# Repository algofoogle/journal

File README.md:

# Anton's Journal

This is a place where I will collect general notes and thoughts on projects I pick up ad-hoc,
or other stuff that takes my interest and I experiment with.

Create a new article with `make` or `make new` (same). Ensure this README is updated correctly at the end, too.

# Index

## 2019

<details>
<summary>Click to open:</summary>

*   [0001-2019-11-28.md](./0001-2019-11-28.md): Digispark tiny Arduino-based minimal USB device.
*   [0002-2019-12-02.md](./0002-2019-12-02.md): Digispark code experiments, Arduino basics, system requirements.
*   [0003-2019-12-03.md](./0003-2019-12-03.md): Digispark virtual keyboard experiments.
*   [0004-2019-12-04.md](./0004-2019-12-04.md): Stuff about installing Arduino libs.
*   ...TBC...
*   [0009-2019-12-19.md](./0009-2019-12-19.md): Quick update re DigiCDC (more minimal USB stuff).
</details>

## 2020

<details>
<summary>Click to open:</summary>

### A lot of 2020 was about FPGA/CPLD/Verilog stuff, starting with entry `0022`

*   [0010-2020-01-06.md](./0010-2020-01-06.md): Blender 3D SVG path offset extrusion, i.e. Straight Skeleton.
*   [0011-2020-01-07.md](./0011-2020-01-07.md): Geeetech A10 3D printer bed adhesion notes.
*   ...TBC...
*   [0021-2020-05-24.md](./0021-2020-05-24.md): FPGA/Verilog getting started; XC9572 CPLD board design initial notes.
*   [0022-2020-05-26.md](./0022-2020-05-26.md): CPLD board, KiCad notes, Xilinx ISE Webpack.
*   [0023-2020-05-29.md](./0023-2020-05-29.md): Lab setup, XC9572XL CPLD board prep notes.
*   [0024-2020-06-02.md](./0024-2020-06-02.md): Quick notes about JLCPCB and other PCB ideas.
*   [0025-2020-06-04.md](./0025-2020-06-04.md): NES Dev board ideas and some thoughts on STM32 types, speed, overclocking.
*   [0026-2020-06-06.md](./0026-2020-06-06.md): Initial tests of DP's XC9572XL CPLD board, Bus Pirate, XSVF player, JTAG.
*   [0027-2020-06-08.md](./0027-2020-06-08.md): Quick notes on my CPLD board, Xilinx ISE on Linux.
*   [0028-2020-06-09.md](./0028-2020-06-09.md): More Xilinx ISE and PACE stuff. Success!
*   [0029-2020-06-15.md](./0029-2020-06-15.md): Following fpga4fun.com on my CPLD board.
*   [0030-2020-06-17.md](./0030-2020-06-17.md): test05f/g/h (music) designs, and working around ISE/Fitter/Synth bugs.
*   [0031-2020-06-19.md](./0031-2020-06-19.md): test05h: Calculating notes.
*   [0032-2020-06-20.md](./0032-2020-06-20.md): CPLD optimisation/fitting and more music box stuff.
*   [0033-2020-06-21.md](./0033-2020-06-21.md): Quick note about starting a Pong-like design.
*   [0034-2020-06-22.md](./0034-2020-06-22.md): Basic VGA output working from by XC9572XL CPLD board.
*   ...TBC...
*   [0046-2020-07-22.md](./0046-2020-07-22.md): Starting CPLD t09a
*   [0047-2020-07-25.md](./0047-2020-07-25.md): CPLD t09a: VGA image from ROM plug-in board
*   [0048-2020-07-29.md](./0048-2020-07-29.md): CPLD t09c rough notes
*   [0049-2020-08-02.md](./0049-2020-08-02.md): CPLD t09d: ROM-based tile map VGA renderer.
*   [0050-2020-08-03.md](./0050-2020-08-03.md): Verilator and vgasim.
*   [0051-2020-08-04.md](./0051-2020-08-04.md): More Verilator: Register initialisation/randomisation.
*   ...TBC...
*   [0057-2020-08-10.md](./0057-2020-08-10.md): Quick notes about GT's (ZipCPU's) Verilator simulation models, re QSPIFLASHSIM.
*   [0058-2020-08-11.md](./0058-2020-08-11.md): Last from 2020: Some FPGA/CPLD/Verilog/Verilator final notes and thoughts about 6502 DMA/Video bus sharing.
</details>

## 2022

<details>
<summary>Click to open:</summary>

*   [0059-2022-04-02.md](./0059-2022-04-02.md): Restart from 2022: Some VirtualBox symlinks stuff under Windows 10 host.
*   [0060-2022-11-23.md](./0060-2022-11-23.md): Loose notes and next steps after Connectorama (ACUcard) first attempt.
</details>

## 2023

<details>
<summary>Click to open:</summary>

*   [0061-2023-04-16.md](./0061-2023-04-16.md): ASIC stuff with a focus on ray casting.
*   [0062-2023-04-17.md](./0062-2023-04-17.md): Fiddling with Raybox ideas.
*   [0063-2023-04-18.md](./0063-2023-04-18.md): Mostly notes about Verilog division and reciprocals.
*   [0064-2023-04-21.md](./0064-2023-04-21.md): Summary of basic fake rendering stuff, and a basic plan for what comes next.
*   [0065-2023-04-23.md](./0065-2023-04-23.md): Quick notes mostly about Verilog
*   [0066-2023-04-26.md](./0066-2023-04-26.md): Lots of notes about TT03 and running Tiny Tapeout GDS build locally
*   [0067-2023-04-27.md](./0067-2023-04-27.md): Some more quick notes about TT03
*   [0068-2023-04-28.md](./0068-2023-04-28.md): Starting fixed-point mode in raybox-app. Notes on VSCode C++ debugging.
*   [0069-2023-04-29.md](./0069-2023-04-29.md): Running Raybox on an FPGA.
*   [0070-2023-04-30.md](./0070-2023-04-30.md): Raybox starting Q16.16. Other future ideas.
*   [0071-2023-05-01.md](./0071-2023-05-01.md): Raybox wall edge glitch fixed! Q16.16 working. What next?
*   [0072-2023-05-02.md](./0072-2023-05-02.md): Raybox map grid boundary glitch fixed.
*   [0073-2023-05-03.md](./0073-2023-05-03.md): Raybox LZC alternatives. Rotation issues.
*   [0074-2023-05-04.md](./0074-2023-05-04.md): Diagnosing/fixing Raybox on FPGA.
*   [0075-2023-05-06.md](./0075-2023-05-06.md): Notes for some Raybox stuff to look at next
*   [0076-2023-05-07.md](./0076-2023-05-07.md): Raybox axis glitch fixed? Other ideas for host control
*   [0077-2023-05-09.md](./0077-2023-05-09.md): Raybox sim builds under Windows now and supports mouse rotation.
*   [0078-2023-05-10.md](./0078-2023-05-10.md): Raybox wall textures, thoughts on RAM
*   [0079-2023-05-12.md](./0079-2023-05-12.md): Raybox improved column rendering/scaling
*   [0080-2023-05-16.md](./0080-2023-05-16.md): Raybox starting work on sprites
*   [0081-2023-05-20.md](./0081-2023-05-20.md): First Raybox sprite seems to project OK
*   [0082-2023-05-22.md](./0082-2023-05-22.md): Raybox sprite extra scaling and screen 640-width
*   [0083-2023-05-23.md](./0083-2023-05-23.md): Tidying Raybox for targeting OpenLane
*   [0084-2023-05-24.md](./0084-2023-05-24.md): Merged Raybox sprites branch. Notes on OpenLane.
*   [0085-2023-05-25.md](./0085-2023-05-25.md): Raybox 64x64 map with multiple wall types supported
*   [0086-2023-05-26.md](./0086-2023-05-26.md): Quick notes on ideas for sending data to the FPGA
*   [0087-2023-05-27.md](./0087-2023-05-27.md): OpenLane experiments with reciprocal approximation design
*   [0088-2023-05-28.md](./0088-2023-05-28.md): Quick notes about LZC and cocotb
*   [0089-2023-06-05.md](./0089-2023-06-05.md): Notes about solo_squash tt03p5 submission
*   [0090-2023-06-06.md](./0090-2023-06-06.md): PC to DE0-Nano bridging ideas inc. IO expanders
*   [0091-2023-06-07.md](./0091-2023-06-07.md): Notes about STM32 USB and virtual COM
*   [0092-2023-06-08.md](./0092-2023-06-08.md): STM32 vs Raspberry Pi Pico
*   [0093-2023-06-09.md](./0093-2023-06-09.md): Follow along with Pi Pico C SDK guide
*   [0094-2023-06-12.md](./0094-2023-06-12.md): Pi Pico to DE0-Nano pin mapping
*   [0095-2023-06-14.md](./0095-2023-06-14.md): Pi Pico stdio coding on Wokwi
*   [0096-2023-06-17.md](./0096-2023-06-17.md): Getting Pico-DE0 REPL working just for GPIO reads
*   [0097-2023-06-18.md](./0097-2023-06-18.md): Pico-DE0 firmware supports basic I/O control now
*   [0098-2023-06-19.md](./0098-2023-06-19.md): Pico-DE0 improvements and readying for Raybox IO
*   [0099-2023-06-20.md](./0099-2023-06-20.md): Notes on Pico-DE0 speed
*   [0100-2023-06-21.md](./0100-2023-06-21.md): Basic plans for next steps in Pico-DE0 and Raybox
*   [0101-2023-06-22.md](./0101-2023-06-22.md): Working on raybox-bridge
*   [0102-2023-06-25.md](./0102-2023-06-25.md): Raybox-bridge time scheduling and USB transfer
*   [0103-2023-06-26.md](./0103-2023-06-26.md): Quick raybox-bridge notes and next steps
*   [0104-2023-06-27.md](./0104-2023-06-27.md): FPGA vga_cursor design works with raybox-bridge. Quartus project notes.
*   [0105-2023-06-29.md](./0105-2023-06-29.md): vga_cursor initial test findings
*   [0106-2023-06-30.md](./0106-2023-06-30.md): Quick update on vga_cursor with circle-cursor test
*   [0107-2023-07-02.md](./0107-2023-07-02.md): Notes on changing vga_cursor to SPI
*   [0108-2023-07-03.md](./0108-2023-07-03.md): vga_cursor now works via SPI
*   [0109-2023-07-06.md](./0109-2023-07-06.md): PicoDeo SPI /cursor command with raybox-bridge support
*   [0110-2023-07-07.md](./0110-2023-07-07.md): Raybox: DE0-Nano builds again. PicoDeo /rbvectors. Windows Verilator notes.
*   [0111-2023-07-10.md](./0111-2023-07-10.md): raybox-bridge basic FPS game state tracking
*   [0112-2023-07-11.md](./0112-2023-07-11.md): raybox-bridge sends vector (view) data, enabling KB/Mouse control in Raybox
*   [0113-2023-07-12.md](./0113-2023-07-12.md): Starting BOOP! game for Lily
*   [0114-2023-07-13.md](./0114-2023-07-13.md): Notes on next steps for Raybox
*   [0115-2023-07-14.md](./0115-2023-07-14.md): Quick notes on VGA DAC and 2D grid collision detection
*   [0116-2023-07-16.md](./0116-2023-07-16.md): raybox-game with basic collision detection
*   [0117-2023-07-18.md](./0117-2023-07-18.md): Thoughts on targeting Tiny Tapeout with Raybox
*   [0118-2023-07-19.md](./0118-2023-07-19.md): Some TT04 ideas
*   [0119-2023-07-22.md](./0119-2023-07-22.md): Let's get started with TT04
*   [0120-2023-07-24.md](./0120-2023-07-24.md): tt04-solo-squash next steps
*   [0121-2023-07-26.md](./0121-2023-07-26.md): Setting up tt04-solo-squash to use solo_squash submodule
*   [0122-2023-07-27.md](./0122-2023-07-27.md): tt04-solo-squash stuff
*   [0123-2023-08-14.md](./0123-2023-08-14.md): Quick update re raybox-zero
*   [0124-2023-08-16.md](./0124-2023-08-16.md): Another quick raybox-zero update
*   [0125-2023-08-18.md](./0125-2023-08-18.md): raybox-zero tracing works
*   [0126-2023-08-19.md](./0126-2023-08-19.md): tt04-raybox-zero started, but gds hardening crashes
*   [0127-2023-08-20.md](./0127-2023-08-20.md): Exploring tt04-raybox-zero synthesis, chasing yosys-abc bug
*   [0128-2023-08-21.md](./0128-2023-08-21.md): Starting tt04-reciprocal test
*   [0129-2023-08-22.md](./0129-2023-08-22.md): tt04-reciprocal findings and next steps on yosys-abc bug hunt
*   [0130-2023-08-23.md](./0130-2023-08-23.md): More yosys-abc bug hunting
*   [0131-2023-08-24.md](./0131-2023-08-24.md): raybox-zero: Improving the FSM
*   [0132-2023-08-25.md](./0132-2023-08-25.md): tt04-raybox-zero harden_test.sh script for stats
*   [0133-2023-08-26.md](./0133-2023-08-26.md): Setting up MPW8 VM again on a new laptop
*   [0134-2023-08-27.md](./0134-2023-08-27.md): raybox-zero SPI access to pov
*   [0135-2023-08-28.md](./0135-2023-08-28.md): raybox-zero sim kb/mouse control and partial POV SPI synth success
*   [0136-2023-08-29.md](./0136-2023-08-29.md): Working on wall_tracer changes
*   [0137-2023-08-30.md](./0137-2023-08-30.md): raybox-zero: Merging height_scaler
*   [0138-2023-08-31.md](./0138-2023-08-31.md): raybox-zero: Minor update
*   [0139-2023-09-01.md](./0139-2023-09-01.md): Improved harden_test, more test results
*   [0140-2023-09-02.md](./0140-2023-09-02.md): raybox-zero test005: Shared multiplier is a winner?
*   [0141-2023-09-03.md](./0141-2023-09-03.md): test006: shmul registered inputs; test007 reg rcp_in
*   [0142-2023-09-04.md](./0142-2023-09-04.md): test008: put a shmul in rcp and mainline test005
*   [0143-2023-09-05.md](./0143-2023-09-05.md): test009 (reducing pov bit ranges); test010 (fixed-point use Q10.10)
*   [0144-2023-09-06.md](./0144-2023-09-06.md): Work on implementing textures
*   [0145-2023-09-08.md](./0145-2023-09-08.md): Notes during TT04 final submission
*   [0146-2023-09-26.md](./0146-2023-09-26.md): VGA DAC PCB
*   [0147-2023-09-27.md](./0147-2023-09-27.md): What next: TT05 etc.
*   [0148-2023-09-28.md](./0148-2023-09-28.md): General updates, looking into VM speed
*   [0149-2023-09-30.md](./0149-2023-09-30.md): SPI flash ROM stuff
*   [0150-2023-10-02.md](./0150-2023-10-02.md): Reading SPI flash ROM using Bus Pirate
*   [0151-2023-10-03.md](./0151-2023-10-03.md): More SPI flash ROM stuff
*   [0152-2023-10-04.md](./0152-2023-10-04.md): Preparing for SPI flash ROM cocotb tests
*   [0153-2023-10-06.md](./0153-2023-10-06.md): SPI flash ROM FPGA tests
*   [0154-2023-10-07.md](./0154-2023-10-07.md): More SPI stuff
*   [0155-2023-10-09.md](./0155-2023-10-09.md): tt05-vga-spi-rom TT05 submission
*   [0156-2023-10-10.md](./0156-2023-10-10.md): tt05-vga-spi-rom improvements
*   [0157-2023-10-11.md](./0157-2023-10-11.md): tt05-vga-spi-rom and cocotb stuff
*   [0158-2023-10-13.md](./0158-2023-10-13.md): A bunch of tt05vsr (tt05-vga-spi-rom) tests
*   [0159-2023-10-14.md](./0159-2023-10-14.md): Continuing tt05vsr (tt05-vga-spi-rom) tests
*   [0160-2023-10-16.md](./0160-2023-10-16.md): Work on raybox-zero update for chipIgnite
*   [0161-2023-10-17.md](./0161-2023-10-17.md): Lots of chipIgnite notes
*   [0162-2023-10-20.md](./0162-2023-10-20.md): raybox-zero textures from external ROM
*   [0163-2023-10-22.md](./0163-2023-10-22.md): Working on QSPI
*   [0164-2023-10-23.md](./0164-2023-10-23.md): Implementing QSPI in tt05vsr and raybox-zero
*   [0165-2023-10-24.md](./0165-2023-10-24.md): raybox-zero OpenLane hardening
*   [0166-2023-10-26.md](./0166-2023-10-26.md): Preparing for chipIgnite
*   [0167-2023-10-27.md](./0167-2023-10-27.md): More prep for chipIgnite
*   [0168-2023-10-28.md](./0168-2023-10-28.md): Again more prep for chipIgnite
*   [0169-2023-10-30.md](./0169-2023-10-30.md): Snippets for other modes of top_ew_algofoogle
*   [0170-2023-10-31.md](./0170-2023-10-31.md): top_ew_algofoogle next steps
*   [0171-2023-11-03.md](./0171-2023-11-03.md): Getting down to the final steps for chipIgnite
*   [0172-2023-11-04.md](./0172-2023-11-04.md): Some fixes to raybox-zero-caravel
*   [0173-2023-11-18.md](./0173-2023-11-18.md): Analog start: installing xschem
*   [0174-2023-11-19.md](./0174-2023-11-19.md): sky130 analog simulation with xschem
*   [0175-2023-11-20.md](./0175-2023-11-20.md): More xschem and sky130
*   [0176-2023-11-22.md](./0176-2023-11-22.md): Tiny update re xschem/sky130
*   [0177-2023-11-27.md](./0177-2023-11-27.md): GFMPW-1 test (gf180mcu)
*   [0178-2023-11-28.md](./0178-2023-11-28.md): GFMPW-1 attempt at raybox-zero
*   [0179-2023-11-30.md](./0179-2023-11-30.md): Quick update re GFMPW-1 attempts
*   [0180-2023-12-01.md](./0180-2023-12-01.md): GFMPW-1 raybox-zero hardening
*   [0181-2023-12-02.md](./0181-2023-12-02.md): Getting algofoogle-multi-caravel up to efabless
*   [0182-2023-12-03.md](./0182-2023-12-03.md): GFMPW-1: Trying to fix UPW harden for gf180-rbz-fsm
*   [0183-2023-12-04.md](./0183-2023-12-04.md): Continue trying to fix rbz-fsm harden for GF180
*   [0184-2023-12-05.md](./0184-2023-12-05.md): First rough success hardening raybox-zero-fsm/UPW
*   [0185-2023-12-06.md](./0185-2023-12-06.md): Mux for GFMPW-1 group submission
*   [0186-2023-12-08.md](./0186-2023-12-08.md): Improving GFMPW-1 muti-project mux and layout
*   [0187-2023-12-09.md](./0187-2023-12-09.md): GFMPW-1 mux and group plan
*   [0188-2023-12-10.md](./0188-2023-12-10.md): GFMPW-1 Finalisation plan for today
*   [0189-2023-12-11.md](./0189-2023-12-11.md): GFMPW-1 finalisation
</details>

## 2024

*   [0190-2024-01-17.md](./0190-2024-01-17.md): PCB assembly with JLC PCB
*   [0191-2024-01-31.md](./0191-2024-01-31.md): Soldering QFNs and GFMPW0 bring-up
*   [0192-2024-02-02.md](./0192-2024-02-02.md): More GFMPW0 bringup prep and other notes
*   [0193-2024-02-03.md](./0193-2024-02-03.md): GFMPW0 smoke test
*   [0194-2024-02-05.md](./0194-2024-02-05.md): Getting TT03p5 ready for demo
*   [0195-2024-03-23.md](./0195-2024-03-23.md): Coming back to life (mostly about a new MPW9 VM)
*   [0196-2024-03-30.md](./0196-2024-03-30.md): TT04 raybox-zero test prep
*   [0197-2024-04-02.md](./0197-2024-04-02.md): Diagnosing tt04-raybox-zero ASIC malfunction
*   [0198-2024-04-03.md](./0198-2024-04-03.md): TT04 bug GL sim; fix VBox VT-x; analog stuff
*   [0199-2024-04-04.md](./0199-2024-04-04.md): Quick update: sky130 and Tiny Tapeout analog design
*   [0200-2024-04-05.md](./0200-2024-05-01.md): Belated update (TT chips, and analog)
*   [0201-2024-05-11.md](./0201-2024-05-11.md): Warming up for TT07 (tt-vga-fun)
*   [0202-2024-05-15.md](./0202-2024-05-15.md): Full layout simulation of tt06-grab-bag
*   [0203-2024-05-20.md](./0203-2024-05-20.md): ngspice full-circuit simulation results and improvements
*   [0204-2024-05-25.md](./0204-2024-05-25.md): Prep resubmission of TT04's raybox-zero to TT07
*   [0205-2024-05-30.md](./0205-2024-05-30.md): Very rough mixed notes about TT07 and starting TT04 testing
*   [0206-2024-06-26.md](./0206-2024-06-26.md): Trying out Efabless eval board and generic Caravel chip
*   [0207-2024-06-28.md](./0207-2024-06-28.md): Testing Caravel chips with HKDebug and the Efabless Eval board
*   [0208-2024-07-05.md](./0208-2024-07-05.md): Trying out CI2311 chips
*   [0209-2024-07-23.md](./0209-2024-07-23.md): Review original binary-weighted current-switching DAC
*   [0210-2024-08-09.md](./0210-2024-08-09.md): Current steering DAC experiments
*   [0211-2024-08-09.md](./0211-2024-08-09.md): Start tt08-vga-fun repo
*   [0212-2024-08-11.md](./0212-2024-08-11.md): Creating layout for tt08-vga-fun's CSDAC
*   [0213-2024-08-16.md](./0213-2024-08-16.md): Completed csdac_nom initial layout for tt08-vga-fun
*   [0214-2024-08-17.md](./0214-2024-08-17.md): Integrating digital and analog blocks in tt08-vga-fun
*   [0215-2024-08-21.md](./0215-2024-08-21.md): New 3x DAC layout and simulation for tt08-vga-fun
*   [0216-2024-08-23.md](./0216-2024-08-23.md): Notes for tt08-vga-fun finalisation inc. segmented CSDAC
*   [0217-2024-09-29.md](./0217-2024-09-29.md): Notes on CI2311 and GFMPW-1 versions of raybox-zero
*   [0218-2024-10-05.md](./0218-2024-10-05.md): GFMPW-1 basic bring-up
*   [0219-2024-10-07.md](./0219-2024-10-07.md): GFMPW-1 bring-up (continued)
*   [0220-2024-10-11.md](./0220-2024-10-11.md): Raybox-zero running on GFMPW-1
*   [0221-2024-10-11.md](./0221-2024-10-11.md): Quick first attempt at TTIHP0p2
*   [0222-2024-11-11.md](./0222-2024-11-11.md): Belated update for TTIHP0p2 and TT09 submissions
*   [0223-2024-11-12.md](./0223-2024-11-12.md): Ideas for future raybox-zero versions, inc. pinout changes
*   [0224-2024-12-05.md](./0224-2024-12-05.md): Rough notes for RBZ and TT06 Analog VGA testing prep

## 2025

*   [0225-2025-01-12.md](./0225-2025-01-12.md): Initial tt06-grab-bag Analog VGA bring-up
*   [0226-2025-02-20.md](./0226-2025-02-20.md): tt06-grab-bag Analog VGA works!
*   [0227-2025-02-25.md](./0227-2025-02-25.md): Efabless shutdown and old notes for TT10 local hardening
*   [0228-2025-03-27.md](./0228-2025-03-27.md): Testing some Tiny Tapeout 7 projects
*   [0229-2025-04-01.md](./0229-2025-04-01.md): tt07-raybox-zero testing (with textures)
*   [0230-2025-04-09.md](./0230-2025-04-09.md): More tt07-raybox-zero testing
*   [0231-2025-04-11.md](./0231-2025-04-11.md): TT06 auto demo; IHP "Antonalog" DAC & ring osc DAC + sim; TTCAD25a & RBZ update notes
*   [0232-2025-09-28.md](./0232-2025-09-28.md): Tiny Tapeouts from June to September
*   [0233-2025-09-28.md](./0233-2025-09-28.md): ttsky25a-vga-matrix-dac
*   [0234-2025-11-11.md](./0234-2025-11-11.md): ttsky25b-vga-matrix-dac (revisited)
*   [0235-2025-11-25.md](./0235-2025-11-25.md): ttgf0p2 submissions

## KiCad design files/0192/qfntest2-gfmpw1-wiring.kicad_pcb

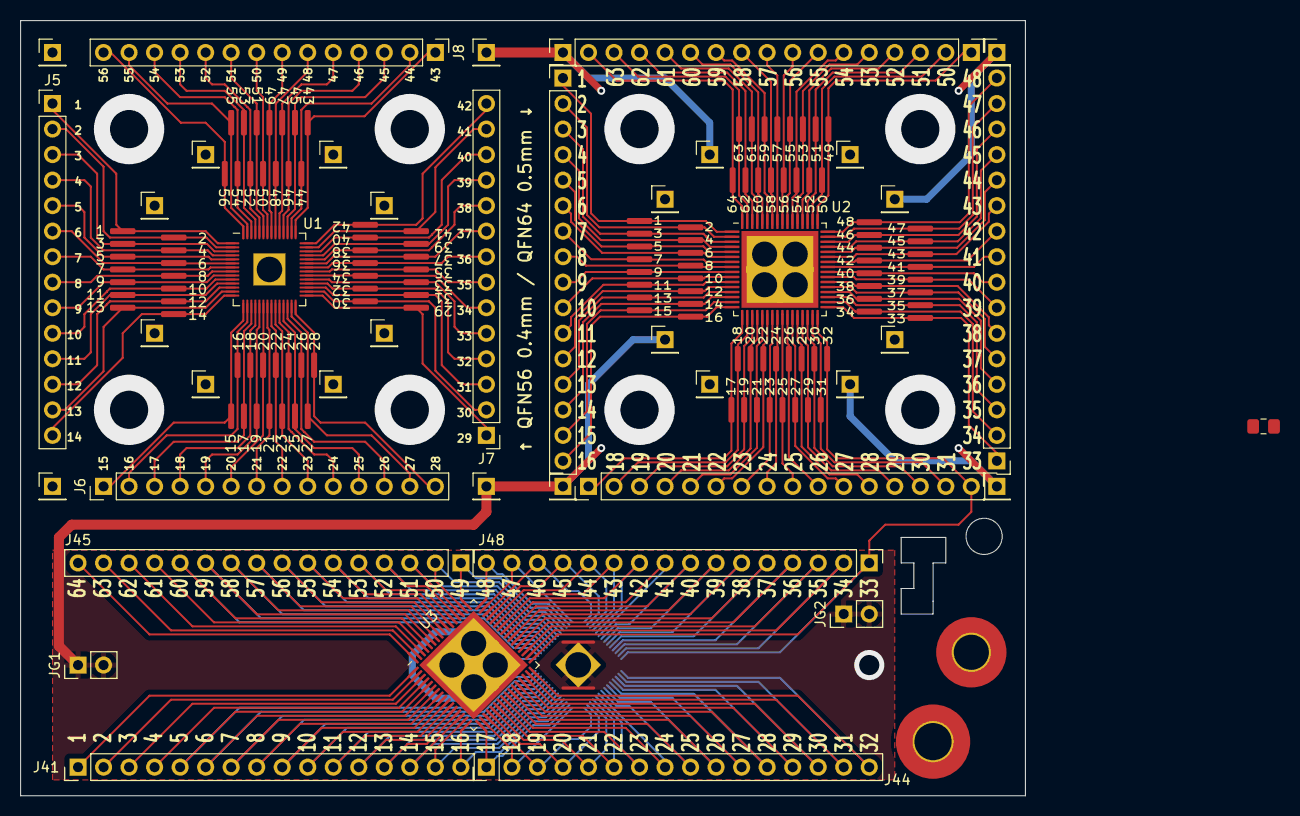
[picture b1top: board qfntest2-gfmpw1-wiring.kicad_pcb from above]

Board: 2 copper layers, 100.0 x 77.1 mm, 50 parts (1 on the bottom side), 184 nets.

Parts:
J1, J2, J3, J4: Conn_01x14; Anton_Pads_01x14_1.27mm_SMD
J5, J6, J7, J8: Conn_01x14; PinHeader_1x14_P2.54mm_Vertical
J9, J10, J11, J12, J13, J14, J15, J16, J17, J18, J19, J20, J29, J30, J31, J32, J33, J34, J35, J36, J37, J38, J39, J40: Conn_01x01; PinHeader_1x01_P2.54mm_Vertical
J21, J22, J23, J24: Conn_01x16; Anton_Pads_01x16_1.27mm_SMD
J25, J26, J27, J28, J41, J44, J45, J48: Conn_01x16; PinHeader_1x16_P2.54mm_Vertical
JG1, JG2: Conn_01x02; PinHeader_1x02_P2.54mm_Vertical
U1, U4: QFN-56-1EP_7x7mm_P0.4mm_EP3.2x3.2mm-HOLE
U2, U3: QFN-64-1EP_9x9mm_P0.5mm_EP7.65x7.65mm-HOLE

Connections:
/U4_01: J44.16, U3.32, U4.1
/U4_02: J44.15, U3.31, U4.2
/U4_03: J44.14, U3.30, U4.3
/U4_04: J44.13, U3.29, U4.4
/U4_05: J44.12, U3.28, U4.5
/U4_06: J44.11, U3.27, U4.6
/U4_07: J44.10, U3.26, U4.7
/U4_08: J44.9, U3.25, U4.8
/U4_09: J44.8, U3.24, U4.9
/U4_10: J44.7, U3.23, U4.10
/U4_11: J44.6, U3.22, U4.11
/U4_12: J44.5, U3.21, U4.12
/U4_13: J44.4, U3.20, U4.13
/U4_14: J44.3, U3.19, U4.14
/U4_15: J44.2, U3.18, U4.15
/U4_16: J44.1, U3.17, U4.16
/U4_17: J41.16, U3.16, U4.17
/U4_18: J41.15, U3.15, U4.18
/U4_19: J41.14, U3.14, U4.19
/U4_20: J41.13, U3.13, U4.20
/U4_21: J41.12, U3.12, U4.21
/U4_22: J41.11, U3.11, U4.22
/U4_23: J41.10, U3.10, U4.23
/U4_24: J41.9, U3.9, U4.24
/U4_25: J41.8, U3.8, U4.25
/U4_26: J41.7, U3.7, U4.26
/U4_27: J41.6, U3.6, U4.27
/U4_28: J41.5, U3.5, U4.28
/U4_29: J45.12, U3.60, U4.29
/U4_30: J45.11, U3.59, U4.30
/U4_31: J45.10, U3.58, U4.31
/U4_32: J45.9, U3.57, U4.32
/U4_33: J45.8, U3.56, U4.33
/U4_34: J45.7, U3.55, U4.34
/U4_35: J45.6, U3.54, U4.35
/U4_36: J45.5, U3.53, U4.36
/U4_37: J45.4, U3.52, U4.37
/U4_38: J45.3, U3.51, U4.38
/U4_39: J45.2, U3.50, U4.39
/U4_40: J45.1, U3.49, U4.40
/U4_41: J48.16, U3.48, U4.41
/U4_42: J48.15, U3.47, U4.42
/U4_43: J48.14, U3.46, U4.43
/U4_44: J48.13, U3.45, U4.44
/U4_45: J48.12, U3.44, U4.45
/U4_46: J48.11, U3.43, U4.46
/U4_47: J48.10, U3.42, U4.47
/U4_48: J48.9, U3.41, U4.48
/U4_49: J48.8, U3.40, U4.49
/U4_50: J48.7, U3.39, U4.50
/U4_51: J48.6, U3.38, U4.51
/U4_52: J48.5, U3.37, U4.52
/U4_53: J48.4, U3.36, U4.53
/U4_54: J48.3, U3.35, U4.54
/U4_55: J48.2, U3.34, U4.55
/U4_56: J22.16, J26.16, J48.1, U2.32, U3.33, U4.56
GND: J9.1, J10.1, J11.1, J12.1, J13.1, J14.1, J15.1, J16.1, J17.1, J18.1, J19.1, J20.1, J29.1, J30.1, J31.1, J32.1, J33.1, J34.1, J35.1, J36.1, J37.1, J38.1, J39.1, J40.1, JG1.1, JG1.2, JG2.1, JG2.2, U1.57 (GND), U2.65 (Foot), U3.65 (Foot), U4.57 (GND)
unnamed: J1.1, J5.1, U1.1
unnamed: J1.2, J5.2, U1.2
unnamed: J1.3, J5.3, U1.3
unnamed: J1.4, J5.4, U1.4
unnamed: J1.5, J5.5, U1.5
unnamed: J1.6, J5.6, U1.6
unnamed: J1.7, J5.7, U1.7
unnamed: J1.8, J5.8, U1.8
unnamed: J1.9, J5.9, U1.9
unnamed: J1.10, J5.10, U1.10
unnamed: J1.11, J5.11, U1.11
unnamed: J1.12, J5.12, U1.12
unnamed: J1.13, J5.13, U1.13
unnamed: J1.14, J5.14, U1.14
unnamed: J2.1, J6.1, U1.15
unnamed: J2.2, J6.2, U1.16
unnamed: J2.3, J6.3, U1.17
unnamed: J2.4, J6.4, U1.18
unnamed: J2.5, J6.5, U1.19
unnamed: J2.6, J6.6, U1.20
unnamed: J2.7, J6.7, U1.21
unnamed: J2.8, J6.8, U1.22
unnamed: J2.9, J6.9, U1.23
unnamed: J2.10, J6.10, U1.24
unnamed: J2.11, J6.11, U1.25
unnamed: J2.12, J6.12, U1.26
unnamed: J2.13, J6.13, U1.27
unnamed: J2.14, J6.14, U1.28
unnamed: J3.1, J7.1, U1.29
unnamed: J3.2, J7.2, U1.30
unnamed: J3.3, J7.3, U1.31
unnamed: J3.4, J7.4, U1.32
unnamed: J3.5, J7.5, U1.33
unnamed: J3.6, J7.6, U1.34
unnamed: J3.7, J7.7, U1.35
unnamed: J3.8, J7.8, U1.36
unnamed: J3.9, J7.9, U1.37
unnamed: J3.10, J7.10, U1.38
unnamed: J3.11, J7.11, U1.39
unnamed: J3.12, J7.12, U1.40
unnamed: J3.13, J7.13, U1.41
unnamed: J3.14, J7.14, U1.42
unnamed: J4.1, J8.1, U1.43
unnamed: J4.2, J8.2, U1.44
unnamed: J4.3, J8.3, U1.45
unnamed: J4.4, J8.4, U1.46
unnamed: J4.5, J8.5, U1.47
unnamed: J4.6, J8.6, U1.48
unnamed: J4.7, J8.7, U1.49
unnamed: J4.8, J8.8, U1.50
unnamed: J4.9, J8.9, U1.51
unnamed: J4.10, J8.10, U1.52
unnamed: J4.11, J8.11, U1.53
unnamed: J4.12, J8.12, U1.54
unnamed: J4.13, J8.13, U1.55
unnamed: J4.14, J8.14, U1.56
unnamed: J21.1, J25.1, U2.1
unnamed: J21.2, J25.2, U2.2
unnamed: J21.3, J25.3, U2.3
unnamed: J21.4, J25.4, U2.4
unnamed: J21.5, J25.5, U2.5
unnamed: J21.6, J25.6, U2.6
unnamed: J21.7, J25.7, U2.7
unnamed: J21.8, J25.8, U2.8
unnamed: J21.9, J25.9, U2.9
unnamed: J21.10, J25.10, U2.10
unnamed: J21.11, J25.11, U2.11
unnamed: J21.12, J25.12, U2.12
unnamed: J21.13, J25.13, U2.13
unnamed: J21.14, J25.14, U2.14
unnamed: J21.15, J25.15, U2.15
unnamed: J21.16, J25.16, U2.16
unnamed: J22.1, J26.1, U2.17
unnamed: J22.2, J26.2, U2.18
unnamed: J22.3, J26.3, U2.19
unnamed: J22.4, J26.4, U2.20
unnamed: J22.5, J26.5, U2.21
unnamed: J22.6, J26.6, U2.22
unnamed: J22.7, J26.7, U2.23
unnamed: J22.8, J26.8, U2.24
unnamed: J22.9, J26.9, U2.25
unnamed: J22.10, J26.10, U2.26
unnamed: J22.11, J26.11, U2.27
unnamed: J22.12, J26.12, U2.28
unnamed: J22.13, J26.13, U2.29
unnamed: J22.14, J26.14, U2.30
unnamed: J22.15, J26.15, U2.31
unnamed: J23.1, J27.1, U2.33
unnamed: J23.2, J27.2, U2.34
unnamed: J23.3, J27.3, U2.35
unnamed: J23.4, J27.4, U2.36
unnamed: J23.5, J27.5, U2.37
unnamed: J23.6, J27.6, U2.38
unnamed: J23.7, J27.7, U2.39
unnamed: J23.8, J27.8, U2.40
unnamed: J23.9, J27.9, U2.41
unnamed: J23.10, J27.10, U2.42
unnamed: J23.11, J27.11, U2.43
unnamed: J23.12, J27.12, U2.44
unnamed: J23.13, J27.13, U2.45
unnamed: J23.14, J27.14, U2.46
unnamed: J23.15, J27.15, U2.47
unnamed: J23.16, J27.16, U2.48
unnamed: J24.1, J28.1, U2.49
unnamed: J24.2, J28.2, U2.50
unnamed: J24.3, J28.3, U2.51
unnamed: J24.4, J28.4, U2.52
unnamed: J24.5, J28.5, U2.53
unnamed: J24.6, J28.6, U2.54
unnamed: J24.7, J28.7, U2.55
unnamed: J24.8, J28.8, U2.56
unnamed: J24.9, J28.9, U2.57
unnamed: J24.10, J28.10, U2.58
unnamed: J24.11, J28.11, U2.59
unnamed: J24.12, J28.12, U2.60
unnamed: J24.13, J28.13, U2.61
unnamed: J24.14, J28.14, U2.62
unnamed: J24.15, J28.15, U2.63
unnamed: J24.16, J28.16, U2.64
unnamed: J41.1, U3.1
unnamed: J41.2, U3.2
unnamed: J41.3, U3.3
unnamed: J41.4, U3.4
unnamed: J45.13, U3.61
unnamed: J45.14, U3.62
unnamed: J45.15, U3.63
unnamed: J45.16, U3.64

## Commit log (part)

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2023-05-02 0072: Raybox map grid boundary glitch fixed
2023-05-02 Minor update to 0072
2023-05-04 0074: Ideas to diagnose/fix Raybox on FPGA
2023-05-04 Updates to 0073 re LZC tests and other theories
2023-05-06 0075: Notes for some Raybox stuff to look at next
2023-05-07 0076: Raybox axis glitch fixed? Other ideas for host control
2023-05-11 0078: Raybox wall textures, thoughts on RAM
2023-05-11 Images for 0078
2023-05-11 Minor edit
2023-05-12 0079: Raybox improved column rendering/scaling
2023-05-20 Starting 0081
2023-05-21 0081: First Raybox sprite seems to project OK
2023-05-23 0083: Tidying Raybox for targeting OpenLane
2023-05-24 0084: Merged Raybox sprites branch. Notes on OpenLane
2023-05-26 0086: Quick notes on ideas for sending data to the FPGA
2023-05-28 0087: OpenLane experiments with reciprocal approximation design
2023-06-05 0089: Notes about solo_squash tt03p5 submission
2023-06-07 0091: Notes about STM32 USB and virtual COM
2023-06-08 0092: STM32 vs Raspberry Pi Pico
2023-06-09 0093: Follow along with Pi Pico C SDK guide
2023-06-09 Updating 0093 re Pi Pico basic USB
2023-06-12 0094 updates
2023-06-12 Adding hero image to 0094
2023-06-14 0095 updates
2023-06-15 Updating README a bit for older entries
2023-06-17 0096: Getting Pico-DE0 REPL working just for GPIO reads
2023-06-17 Just testing...
2023-06-17 0096 has link to previous journal in preamble now
2023-06-17 Update 0096, plus some backlinks, and improve Makefile
2023-06-17 Makefile minor correction
2023-06-17 0096 updated for extra pico_de0 firmware options
2023-06-19 0098: Pico-DE0 improvements and readying for Raybox IO
2023-06-19 Update 0098 re python client started
2023-06-20 0099: Notes on Pico-DE0 speed
2023-06-22 0101: Working on raybox-bridge
2023-06-22 0101 update
2023-06-25 0102: Raybox-bridge time scheduling and USB transfer
2023-06-26 0103: Quick raybox-bridge notes
2023-06-27 0104: FPGA vga_cursor design works with raybox-bridge. Quartus project notes
2023-06-29 0105: vga_cursor initial test findings
2023-06-30 0106: Quick update on vga_cursor with circle-cursor test
2023-06-30 Update 0106 with pictures
2023-07-02 0107 updates for USE_SPI update and next steps
2023-07-03 0108: vga_cursor now works via SPI
2023-07-07 0110: Raybox: DE0-Nano builds again. Windows Verilator notes
2023-07-07 Update 0110 with PicoDeo /rbvectors info
2023-07-10 0111: raybox-bridge basic FPS game state tracking
2023-07-11 Update 0112 re Raybox now actually receiving SPI vectors data
2023-07-12 0113: Starting BOOP! game for Lily
2023-07-14 0115: Quick notes on VGA DAC and 2D grid collision detection
2023-07-16 0116: raybox-game with basic collision detection
2023-07-19 0118: Some TT04 ideas
2023-07-22 0119: Let's get started with TT04
2023-07-24 0120 updates
2023-07-26 0121: Setting up tt04-solo-squash to use solo_squash submodule
2023-07-27 0122: tt04-solo-squash stuff
2023-07-27 Update 0122
2023-08-16 Minor extra info on 0123
2023-08-16 0124: Another quick raybox-zero update
2023-08-16 More updates to 0124
2023-08-18 0125: raybox-zero tracing works
2023-08-18 More notes on 0125
2023-08-19 Update 0126 for trying to locally run hardening per TT04
2023-08-19 Update 0126 with progress on local hardening
2023-08-20 Update 0127 with new OpenLane container launch instructions
2023-08-20 Minor update to 0127
2023-08-21 0128: Starting tt04-reciprocal test
2023-08-22 0129: tt04-reciprocal findings and next steps on yosys-abc bug hunt
2023-08-23 Lots of updates on 0129 and 2308B
2023-08-23 0130: More yosys-abc bug hunting
2023-08-24 0131: raybox-zero: Improving the FSM
2023-08-24 Logging initial results for 0131
2023-08-26 0133: Setting up MPW8 VM again on a new laptop
2023-08-26 Updates to 0133 re MPW8 VM setup
2023-08-27 Update 0133 re VSCode
2023-08-27 0134: raybox-zero SPI access to pov
2023-08-28 Update 0135 with synth results
2023-08-29 0136: Working on wall_tracer changes
2023-08-29 Updates to 0136 re working shared_reciprocal
2023-08-29 Update 0136: Adding stats before shared_reciprocal
2023-08-30 0137: raybox-zero: Merging height_scaler
2023-08-30 Update 0137 with stats from debug logic baked in
2023-08-31 0138: raybox-zero: Minor update
2023-09-01 Update 0139 with baseline harden_test results: height_scaler merged into wall_tracer
2023-09-01 Update 0139: Results for test001 (Merged TraceStep/TraceTest; commented out 'tex' logic)
2023-09-01 Update 0139: Add extra test001 data
2023-09-01 Update 0139: Results for test002: registered vdist
2023-09-01 Update 0139: Adding test004 results and a couple other ideas
2023-09-02 0140: raybox-zero test005: Shared multiplier is a winner?
2023-09-03 0141: test006
2023-09-03 Update 0141 with test006 alternate
2023-09-04 0142: test008: put a shmul in rcp
2023-09-04 Minor 0142 update
2023-09-04 Update 0142 after mainlining test005
2023-09-05 Update 0143 with extra test009 results
2023-09-05 Update 0143 to describe findings of test009-2, -3, and -4
2023-09-05 Update 0143 with GDS image of 2x2 and comments on power
2023-09-05 Minor update to 0143
2023-09-06 Update 0143: test010-4 Q10.10 results
2023-09-06 Start 0144: Work on implementing texturs
2023-09-26 Add tip 2309A
2023-09-26 0146: VGA DAC PCB
2023-09-27 0147: What next: TT05 etc.
2023-09-27 Update 0147 with notes about wall/sprite memory access
2023-09-30 Update 0148 with recent fixes and next steps
2023-09-30 0149: SPI flash ROM stuff
2023-10-02 Update 0149 with a few other links
2023-10-02 0150: Reading SPI flash ROM using Bus Pirate
2023-10-03 0151: More SPI flash ROM stuff
2023-10-03 Stub 0152
2023-10-04 Tip 2310A: Setting up Python on Windows with VSCode
2023-10-06 0153: SPI flash ROM FPGA tests
2023-10-06 Update 0153: Add ROM data sample
2023-10-07 0154: More SPI stuff
2023-10-07 Update 0154 a little
2023-10-07 Update 0154 re stored-vs-direct and other next steps
2023-10-08 Stub 0155: Continuing SPI test design
2023-10-09 Stub 0156: tt05-vga-spi-rom improvements
2023-10-09 Minor updates to 0155
2023-10-10 Tip 2310B (cocotb, iverilog, gtkwave on Windows); 0156 lots of cocotb testing doco
2023-10-10 Various minor updates
2023-10-10 Minor 0156 update re spiflash
2023-10-11 Adding to 0157
2023-10-12 Finish 0157
2023-10-14 0158: A bunch of tt05vsr (tt05-vga-spi-rom) tests
2023-10-14 Stub 0159
2023-10-14 Lots of updates for 0159 test results
2023-10-14 Updated 0159 a little bit
2023-10-16 0160: Work on raybox-zero update for chipIgnite
2023-10-16 Update 0160
2023-10-20 0161: Lots of chipIgnite notes
2023-10-20 Stub 0162
2023-10-20 Update 0162
2023-10-20 Update 0162: First SPI write test of wall texture test image (wolfwall)
2023-10-20 Update 0162: Fix texture orientation and light/dark tint
2023-10-20 Update 0162 with notes re QSPI
2023-10-22 Stub 0163
2023-10-22 0163: Working on QSPI - progress update
2023-10-22 Update 0163: Many more SQPI notes
2023-10-22 Update 0163: TL;DR added for QSPI process
2023-10-22 Minor 0163 update
2023-10-23 Update 0164 with plan for tt05vsr QSPI reads
2023-10-23 0164: Implementing QSPI in tt05vsr and raybox-zero
2023-10-24 Update 0165 re plan, Quartus PLL, SPI glitch RC filter idea, wall edge glitch, extra rbzero features
2023-10-24 Minor 0165 update
2023-10-24 Minor 0165 update re hardening
2023-10-24 Update 0165 with lots of hardening details
2023-10-27 0166: Preparing for chipIgnite
2023-10-27 Stub 0167
2023-10-28 0168: Again more prep for chipIgnite
2023-10-28 Prior updates to 0165; working out pads
2023-10-28 Update 0168 with a few more notes
2023-10-29 Big updates on 0168 re SNIPPET1_NoShare
2023-10-29 Minor updates to 0168
2023-10-30 Update 0169 with some harden test results
2023-10-30 Update 0169 with hardening results up to at13
2023-10-31 0170: top_ew_algofoogle next steps
2023-11-01 Update 0170 with a bunch of new raybox-zero stuff
2023-11-03 0171: Getting down to the final steps for chipIgnite
2023-11-04 Close off 0171 notes from yesterday
2023-11-18 Minor update to 0168
2023-11-18 0173: Analog start: installing xschem
2023-11-21 0175: More xschem and sky130
2023-11-21 Update 0175 re 01_inverter design test
2023-11-27 0176: Tiny update re xschem/sky130
2023-11-27 Stub 0177
2023-11-27 Lots of updates to 0177
2023-11-27 Updating 0177 with next steps
2023-11-28 0178: GFMPW-1 attempt at raybox-zero
2023-12-01 Update 0180
2023-12-02 Update 0180 per raybox-zero successful GF180 harden
2023-12-02 Update 0181
2023-12-02 Update 0181: Extra notes and list of REPLACEME_... stuff
2023-12-03 0182: GFMPW-1: Trying to fix UPW harden for gf180-rbz-fsm
2023-12-03 Update 0182: Test 3 UPW results
2023-12-03 Minor 0182 update
2023-12-03 WIP on 0182 for more tests
2023-12-03 More 0182 updates
2023-12-04 0183: Continue trying to fix rbz-fsm harden for GF180
2023-12-04 Add extra notes to 0183
2023-12-05 0184: First rough success hardening raybox-zero-fsm/UPW
2023-12-05 Minor update 0184
2023-12-05 Update 0184: Add success-6 data
2023-12-05 Update 0184: success-8 data
2023-12-05 Update 0184: Adding comparisons
2023-12-05 Update 0184: Add success-9 and next steps
2023-12-06 0185: Quick notes on sharing the GFMPW-1 submission
2023-12-07 0185: Mux for GFMPW-1 group submission
2023-12-09 Stub 0187
2023-12-09 0187: GFMPW-1 mux and group plan
2023-12-09 Update 0187 with die layout
2023-12-09 Stub 0188
2023-12-10 0188: GFMPW-1 Finalisation plan for today
2023-12-10 Updates to 0188
2023-12-11 0189: GFMPW-1 finalisation
2023-12-21 Stub 0190
2024-01-16 Replace 0190 (because it was empty) and start JLC PCBA update
2024-01-16 Minor updates for 0190
2024-01-30 0190: Lots of updates re JLC PCBA trial design and submission
2024-02-01 Update 0191: Improving Caravel pinout diagram
2024-02-02 0192: More GFMPW0 bringup prep and other notes
2024-02-03 Update 0192: GFMPW0 breakout 'bodge' soldering plan
2024-02-03 Stub 0193
2024-02-04 0193: GFMPW0 smoke test
2024-02-05 Stub 0194
2024-02-06 Update 0192: Add progress on VGA clock PCB revs
2024-03-23 0195: Coming back to life (mostly about a new MPW9 VM)
2024-03-30 Stub 0196
2024-03-30 0196: TT04 raybox-zero test prep
2024-04-02 0197: Diagnosing tt04-raybox-zero ASIC malfunction
2024-04-02 Update 0197 with more testing results and possible 'pin swap' bug reference
2024-04-03 0198: TT04 bug GL sim; fix VBox VT-x; analog stuff
2024-04-04 Stub 0199
2024-04-05 Stub 200
2024-04-09 Quick 0198 fix for video embedding in GFM
2024-04-30 0200: Belated update (TT chips, and analog)
2024-05-10 Stub 0201
2024-05-11 0201: Warming up for TT07 (tt-vga-fun)
2024-05-19 0202: Full layout simulation of tt06-grab-bag
2024-05-19 Stub 0203
2024-05-24 Updates to 0202 and 0203 re more tt-vga-fun ideas on TT07
2024-05-24 Stub 0204
2024-05-28 Updates to 0204 re TT04 raybox-zero rehardening steps
2024-05-29 Big updates on 0204 for running TT04/TT07 raybox-zero RTL/GL tests
2024-06-25 0205: Very rough mixed notes about TT07 and starting TT04 testing
2024-06-27 0206: Trying out Efabless eval board and generic Caravel chip
2024-07-05 Minor update
2024-07-05 Stub 0208
2024-07-22 Stub 0209
2024-08-09 0209: Review original binary-weighted current-switching DAC
2024-08-09 0210: Current steering DAC experiments
2024-08-11 0211: Start tt08-vga-fun repo
2024-08-11 Stub 0212
2024-08-16 Stub 0213
2024-08-16 02123: Completed csdac_nom initial layout for tt08-vga-fun
2024-08-16 Stub 0214
2024-08-20 0214: Integrating digital and analog blocks in tt08-vga-fun
2024-08-21 0215: Simulation and next steps for tt08-vga-fun
2024-08-23 Update 0215
2024-10-04 0216: Notes for tt08-vga-fun finalisation inc. segmented CSDAC
2024-10-05 0217: Notes on CI2311 and GFMPW-1 versions of raybox-zero
2024-10-07 Tie off 0218, start 0219
2024-10-08 0219: GFMPW-1 bring-up (continued)
2024-10-11 Update 0219 with more GFMPW-1 testing notes
2024-10-11 Stub 0220
2024-10-11 Stub 0221
2024-10-19 Stub 0222
2024-12-04 0222: Belated update for TTIHP0p2 and TT09 submissions
2024-12-04 Stub 0224
2025-01-12 Rough updates for 0224 re Analog Discovery 3 and opamp test board
2025-02-20 0226: tt06-grab-bag Analog VGA works!
2025-02-21 Add more detail to 0226
2025-02-23 Finishing off 0226 re tt06-grab-bag
2025-02-24 Stub 0227
2025-04-08 0229: tt07-raybox-zero testing (with textures)
2025-04-08 Minor corrections to 0229
2025-09-28 0231: TT06 auto demo; IHP "Antonalog" DAC & ring osc DAC + sim; TTCAD25a & RBZ update notes
2025-09-28 0232: Tiny Tapeouts from June to September
2026-01-02 0234: ttsky25b-vga-matrix-dac (revisited)
